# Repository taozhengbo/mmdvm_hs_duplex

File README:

# MMDVM_HS_Hat_Duplex
MMDVM_HS Hat Duplex Ver for the Raspberry Pi 

This project provides a Raspberry Pi Hat for the [MMDVM_HS Hotspot](https://github.com/juribeparada/MMDVM_HS). It was designed for the Raspberry Pi any Version, but should work on any other Pi with the Hat interface. 

First revisions of the board have been built successfully!

The PCB is designed in KiCad and the necessary libraries are included. The supplied Gerber files can be used to order PCBs, for example at Elecrow or DirtyPCBs. 

### Revision 1.0 2018-1.25 Tested OK

Either the ADF7021 or the ADF7021-N can be used. Define the proper version in the firmware!

## Firmware Installation
For specific details about the firmware installation, check [these](https://github.com/juribeparada/MMDVM_HS#build-de-firmware-and-upload-to-zumspot-rpi) instructions.  

Enable the following settings in Config.h:

    #define MMDVM_HS_HAT_REV12
    #define ENABLE_ADF7021
    #define ADF7021_14_7456
    #define STM32_USART1_HOST
    #define ENABLE_SCAN_MODE
    #define DUPLEX
it work both DUPLEX or no DUPLEX mode,when in DUPLEX Mode Main RF is TX,Second RF is RX    
Build the firmware:

    make

And finally upload the firmware to the MMDVM_HS_Hat:

    sudo make mmdvm_hs_hat

## License
This project is released under the Creative Commons Attribution-NonCommercial-ShareAlike 3.0 (CC-BY-NC-SA 3.0, https://creativecommons.org/licenses/by-nc-sa/3.0/) license. You may edit and share it as you like, as long as credit is given and the license is not changed. You can build as many boards for you and your friends as you like and you can even sell it to them to cover your costs, **however it is strictly forbidden to turn this into a commercial product! You are not allowed to build and sell these boards for profit!**

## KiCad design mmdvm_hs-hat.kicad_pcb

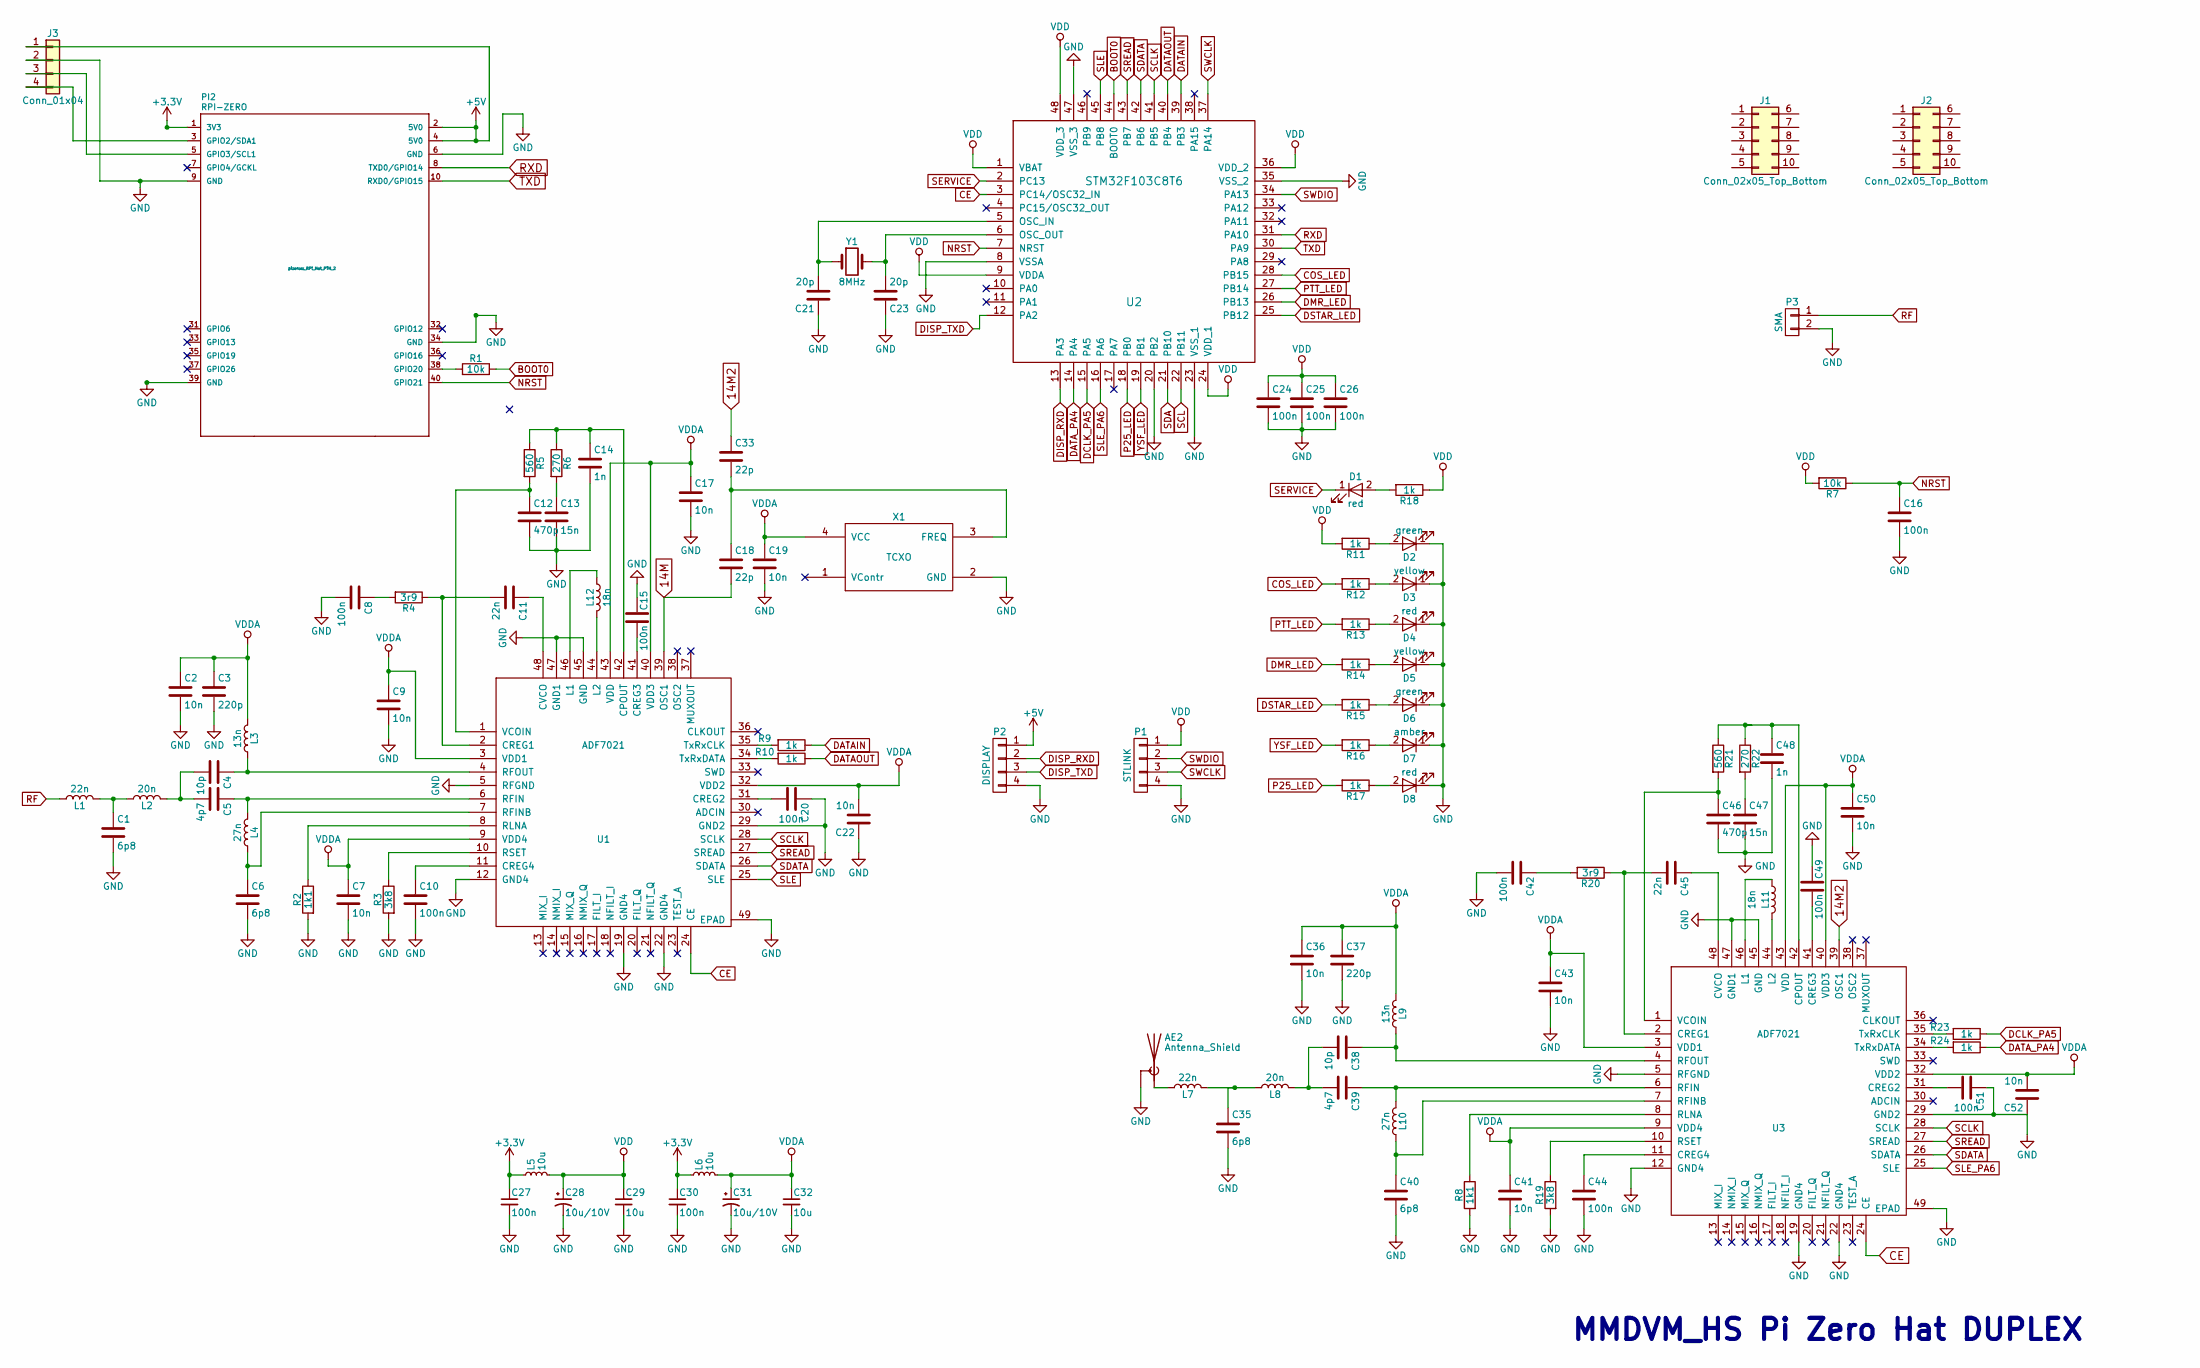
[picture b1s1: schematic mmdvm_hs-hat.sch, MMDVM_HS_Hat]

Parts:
AE2: Antenna_Shield; SMA_THT_Jack_Straight
C1, C6, C35, C40: 6p8; C_0603; MPN GJM1555C1H6R8BB01D
C2, C7, C9, C17, C19, C22, C36, C41, C43, C50, C52: 10n; C_0603; MPN GRM155R71H103KA88D
C3, C37: 220p; C_0603; MPN GRM1555C1H221JA01D
C4, C38: 10p; C_0603; MPN GRM0225C1C100JA03L
C5, C39: 4p7; C_0603; MPN GRM1555C1H4R7CA01D
C8, C10, C15, C16, C20, C24, C25, C26, C42, C44, C49, C51: 100n; C_0603; MPN GRM022R60J104KE15L
C11, C45: 22n; C_0603; MPN GCM155R71E223KA55D
C12, C46: 470p; C_0603; MPN GRM155R71H471KA01D
C13, C47: 15n; C_0603; MPN GRM155R71C153KA01D
C14, C48: 1n; C_0603; MPN GRM155R60J105KE19D
C18, C33: 22p; C_0603; MPN 04025A220GAT2A
C21, C23: 20p; C_0603; MPN GJM1555C1H200FB01D
C27, C30: 100n; C_0603
C28, C31: 10u/10V; CP_Tantalum_Case-A_EIA-3216-18_Reflow
C29, C32: 10u; C_0603
D1, D4, D8: red; LED_0603; MPN SML-P12U2TT86R
D2, D6: green; LED_0603; MPN SML-P13PTT86R
D3, D5: yellow; LED_0603; MPN SML-P12WTT86R
D7: amber; LED_0603; MPN SML-P12DTT86R
J1, J2: Conn_02x05_Top_Bottom; Pin_Header_Straight_2x05_Pitch2.54mm_SMD
J3: Conn_01x04; Pin_Header_Straight_1x04_Pitch2.54mm
L1, L7: 22n; L_0603; MPN 0402AF-220XJLU
L2, L8: 20n; L_0603; MPN 36501E20NJTDG
L3, L9: 13n; L_0603; MPN 0402CS-13NXJLU
L4, L10: 27n; L_0603; MPN 0402CS-27NXJLU
L5, L6: 10u; L_0603
L11, L12: 18n; L_0603; MPN 0402CS-13NXJLU
P1: STLINK; Pin_Header_Straight_1x04_Pitch2.54mm; MPN 826629-4
P2: DISPLAY; Pin_Header_Straight_1x04_Pitch2.54mm; MPN 826629-4
P3: SMA; SMA_THT_Jack_Straight; MPN 5-1814832-1
PI2: RPI-ZERO; z_RPi_Hat_PTH_2
R1, R7: 10k; R_0603; MPN CRCW040210K0FKED
R2, R8: 1k1; R_0603; MPN RR0510P-112-D
R3, R19: 3k8; R_0603; MPN RR0510P-3831-D
R4, R20: 3r9; R_0603; MPN CRCW04023R90FKED
R5, R21: 560; R_0603; MPN ERA-2AEB561X
R6, R22: 270; R_0603; MPN ERA-2AEB271X
R9, R10, R11, R12, R13, R14, R15, R16, R17, R18, R23, R24: 1k; R_0603; MPN ERJ-PA2D1001X
U1: ADF7021; QFN-48-1EP_7x7mm_Pitch0.5mm; MPN ADF7021BCPZ
U2: STM32F103C8T6; LQFP-48_7x7mm_Pitch0.5mm; MPN STM32F103C8T6
U3: ADF7021; _ADF7021_QFN-48-1EP_7x7mm_Pitch0.5mm
X1: TCXO; Oscillator_SMD_TXC_7C-4pin_5.0x3.2mm; MPN ECS-TXO-3225-147.4-TR
Y1: 8MHz; Crystal_SMD_Abracon_ABM3-2pin_5.0x3.2mm; MPN ABM3-8.000MHz-D2Y-T

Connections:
14M: C18.2, U1.39 (OSC1)
14M2: C33.1, U3.39 (OSC1)
+3V3: C27.1, C30.1, L5.1, L6.1, PI2.1 (3V3)
+5V: J3.1, P2.1, PI2.2 (5V0), PI2.4 (5V0)
BOOT0: R1.1, U2.44 (BOOT0)
CE: U1.24 (CE), U2.3 (PC14/OSC32_IN), U3.24 (CE)
COS_LED: R12.2, U2.28 (PB15)
DATAIN: R9.1, U2.39 (PB3)
DATAOUT: R10.1, U2.40 (PB4)
DATA_PA4: R24.1, U2.14 (PA4)
DCLK_PA5: R23.1, U2.15 (PA5)
DISP_RXD: P2.2, U2.13 (PA3)
DISP_TXD: P2.3, U2.12 (PA2)
DMR_LED: R14.2, U2.26 (PB13)
DSTAR_LED: R15.2, U2.25 (PB12)
GND: AE2.2 (Shield), C1.2, C2.2, C3.2, C6.2, C7.2, C8.2, C9.2, C10.2, C12.2, C13.2, C14.2, C15.1, C16.2, C17.2, C19.2, C20.1, C21.1, C22.1, C23.1, C24.2, C25.2, C26.2, C27.2, C28.2, C29.2, C30.2, C31.2, C32.2, C35.2, C36.2, C37.2, C40.2, C41.2, C42.2, C43.2, C44.2, C46.2, C47.2, C48.2, C49.1, C50.2, C51.1, C52.1, D2.1 (K), D3.1 (K), D4.1 (K), D5.1 (K), D6.1 (K), D7.1 (K), D8.1 (K), J3.2, P1.4, P2.4, P3.2, PI2.6 (GND), PI2.9 (GND), PI2.34 (GND), PI2.39 (GND), R2.2, R3.2, R8.2, R19.2, U1.5 (RFGND), U1.12 (GND4), U1.19 (GND4), U1.22 (GND4), U1.29 (GND2), U1.45 (GND), U1.47 (GND1), U1.49 (EPAD), U2.8 (VSSA), U2.20 (PB2), U2.23 (VSS_1), U2.35 (VSS_2), U2.47 (VSS_3), U3.5 (RFGND), U3.12 (GND4), U3.19 (GND4), U3.22 (GND4), U3.29 (GND2), U3.45 (GND), U3.47 (GND1), U3.49 (EPAD), X1.2 (GND)
NRST: C16.1, PI2.40 (GPIO21), R7.1, U2.7 (NRST)
unnamed: AE2.1 (A), L7.1
unnamed: C1.1, L1.2, L2.1
unnamed: C4.1, L3.1, U1.4 (RFOUT)
unnamed: C4.2, C5.2, L2.2
unnamed: C5.1, L4.2, U1.6 (RFIN)
unnamed: C6.1, L4.1, U1.7 (RFINB)
unnamed: C8.1, R4.2
unnamed: C10.1, U1.11 (CREG4)
unnamed: C11.1, U1.48 (CVCO)
unnamed: C11.2, R4.1, U1.2 (CREG1)
unnamed: C12.1, R5.2, U1.1 (VCOIN)
unnamed: C13.1, R6.2
unnamed: C14.1, R5.1, R6.1, U1.42 (CPOUT)
unnamed: C15.2, U1.41 (CREG3)
unnamed: C18.1, C33.2, X1.3 (FREQ)
unnamed: C20.2, U1.31 (CREG2)
unnamed: C21.2, U2.5 (OSC_IN), Y1.1
unnamed: C23.2, U2.6 (OSC_OUT), Y1.2
unnamed: C35.1, L7.2, L8.1
unnamed: C38.1, L9.1, U3.4 (RFOUT)
unnamed: C38.2, C39.2, L8.2
unnamed: C39.1, L10.2, U3.6 (RFIN)
unnamed: C40.1, L10.1, U3.7 (RFINB)
unnamed: C42.1, R20.2
unnamed: C44.1, U3.11 (CREG4)
unnamed: C45.1, U3.48 (CVCO)
unnamed: C45.2, R20.1, U3.2 (CREG1)
unnamed: C46.1, R21.2, U3.1 (VCOIN)
unnamed: C47.1, R22.2
unnamed: C48.1, R21.1, R22.1, U3.42 (CPOUT)
unnamed: C49.2, U3.41 (CREG3)
unnamed: C51.2, U3.31 (CREG2)
unnamed: D1.2 (A), R18.2
unnamed: D2.2 (A), R11.1
unnamed: D3.2 (A), R12.1
unnamed: D4.2 (A), R13.1
unnamed: D5.2 (A), R14.1
unnamed: D6.2 (A), R15.1
unnamed: D7.2 (A), R16.1
unnamed: D8.2 (A), R17.1
unnamed: J3.3, PI2.5 (GPIO3/SCL1)
unnamed: J3.4, PI2.3 (GPIO2/SDA1)
unnamed: L11.1, U3.46 (L1)
unnamed: L11.2, U3.44 (L2)
unnamed: L12.1, U1.46 (L1)
unnamed: L12.2, U1.44 (L2)
unnamed: PI2.38 (GPIO20), R1.2
unnamed: R2.1, U1.8 (RLNA)
unnamed: R3.1, U1.10 (RSET)
unnamed: R8.1, U3.8 (RLNA)
unnamed: R9.2, U1.35 (TxRxCLK)
unnamed: R10.2, U1.34 (TxRxDATA)
unnamed: R19.1, U3.10 (RSET)
unnamed: R23.2, U3.35 (TxRxCLK)
unnamed: R24.2, U3.34 (TxRxDATA)
P25_LED: R17.2, U2.18 (PB0)
PTT_LED: R13.2, U2.27 (PB14)
RF: L1.1, P3.1
RXD: PI2.8 (TXD0/GPIO14), U2.31 (PA10)
SCL: U2.22 (PB11)
SCLK: U1.28 (SCLK), U2.41 (PB5), U3.28 (SCLK)
SDA: U2.21 (PB10)
SDATA: U1.26 (SDATA), U2.42 (PB6), U3.26 (SDATA)
SERVICE: D1.1 (K), U2.2 (PC13)
SLE: U1.25 (SLE), U2.45 (PB8)
SLE_PA6: U2.16 (PA6), U3.25 (SLE)
SREAD: U1.27 (SREAD), U2.43 (PB7), U3.27 (SREAD)
SWCLK: P1.3, U2.37 (PA14)
SWDIO: P1.2, U2.34 (PA13)
TXD: PI2.10 (RXD0/GPIO15), U2.30 (PA9)
VDD: C24.1, C25.1, C26.1, C28.1, C29.1, L5.2, P1.1, R7.2, R11.2, R18.1, U2.1 (VBAT), U2.9 (VDDA), U2.24 (VDD_1), U2.36 (VDD_2), U2.48 (VDD_3)
VDDA: C2.1, C3.1, C7.1, C9.1, C17.1, C19.1, C22.2, C31.1, C32.1, C36.1, C37.1, C41.1, C43.1, C50.1, C52.2, L3.2, L6.2, L9.2, U1.3 (VDD1), U1.9 (VDD4), U1.32 (VDD2), U1.40 (VDD3), U1.43 (VDD), U3.3 (VDD1), U3.9 (VDD4), U3.32 (VDD2), U3.40 (VDD3), U3.43 (VDD), X1.4 (VCC)
YSF_LED: R16.2, U2.19 (PB1)

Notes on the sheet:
MMDVM_HS Pi Zero Hat DUPLEX

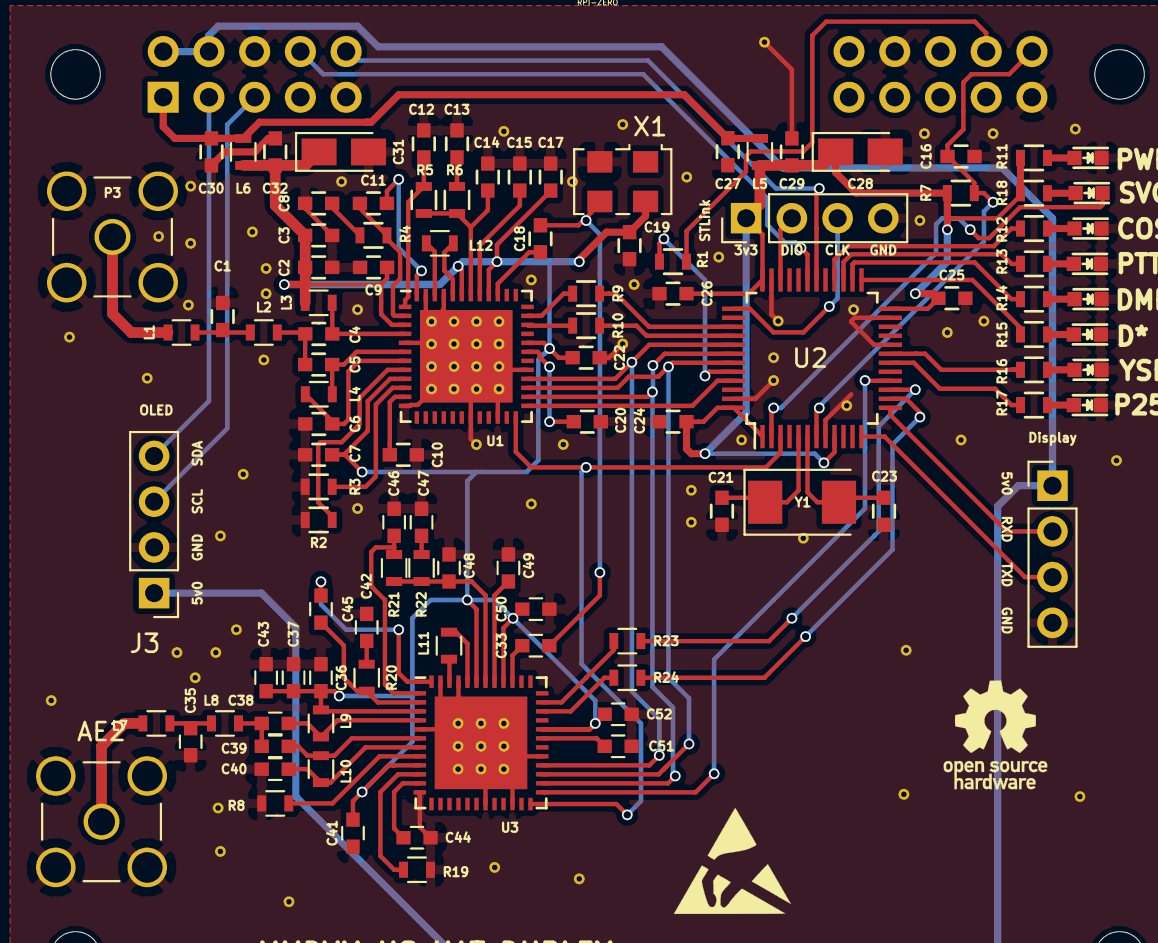
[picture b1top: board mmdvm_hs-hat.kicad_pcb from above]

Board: 2 copper layers, 106 parts (0 on the bottom side), 88 nets.

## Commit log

2018-01-27 V1.0

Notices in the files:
mmdvm_hs-hat.kicad_pcb:
(c) 2018 BG7IYN  V1.0
cc-by-nc-sa
